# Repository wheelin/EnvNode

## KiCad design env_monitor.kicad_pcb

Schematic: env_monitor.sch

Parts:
C1, C2, C6, C7, C9, C12, C27, C28, C29, C30, C31, C32, C33, C34, C35: 1u; C_0805_HandSoldering
C3, C5, C22, C24: 4.7u; C_0805_HandSoldering
C4, C11, C13, C14, C16, C17, C19, C20, C23, C25: 100n; C_0805_HandSoldering
C8, C10: 47p; C_0805_HandSoldering
C15, C26: 10n; C_0805_HandSoldering
C18, C21: 20p; C_0805_HandSoldering
D1: LED_RGB; LED_RGB_PLCC-6
D2: RX_R; LED_0805_HandSoldering
D3: TX_G; LED_0805_HandSoldering
D4: BAT54KFILM; D_SOD-523
J1: Conn_01x02; JST_PH_B2B-PH-SM4-TB_02x2.00mm_Straight
J2: USB_B_Micro; USB_Micro-B_Molex_47346-0001
J3, J4: Conn_01x06; Pin_Header_Straight_1x06_Pitch2.54mm
J5: Micro_SD_Card_Det_Hirose_DM3AT; Hirose_DM3AT-SF-PEJM5
J6: Conn_01x03; MS12ANW03
L1: BKP2125HS600-T; L_0805_HandSoldering
R1, R2, R3, R8, R9, R12, R13, R14, R15, R16, R17, R20: 10k; R_0805_HandSoldering
R4: 20k; R_0805_HandSoldering
R5, R23: 750; R_0805_HandSoldering
R6, R7, R24: 330; R_0805_HandSoldering
R10, R22, R25, R28, R29, R32, R33: 47k; R_0805_HandSoldering
R11, R26, R27: 100k; R_0805_HandSoldering
R18: 4.7k; R_0805_HandSoldering
R19, R21: 27; R_0805_HandSoldering
SW1, SW2, SW4, SW5, SW6: SW_Push; SW_SPST_B3S-1000
U1: lmv341; SOT-23-6_Handsoldering
U2: TPS73633DBV; SOT-23-5_HandSoldering
U3: FT230XS; SSOP-16_3.9x4.9mm_Pitch0.635mm
U4: STM32L431CCTx; LQFP-48_7x7mm_Pitch0.5mm
U5: STLCS01V1; STLC01V1
U6: DOGM128X6; DOGM128E
Y1: Crystal_GND24; Crystal_SMD_Abracon_ABM3B-4pin_5.0x3.2mm

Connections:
FRX_MTX: U3.4, U4.21 (PB10)
FTX_MRX: U3.1, U4.22 (PB11)
IO_MCU_RST: C15.1, J3.5, R22.2, U4.7 (NRST)
IO_MCU_SWCLK: J3.2, U4.37 (PA14)
IO_MCU_SWDIO: J3.4, U4.34 (PA13)
LCD_CMD_DAT: U4.19 (PB1), U6.24
LCD_CS: R27.2, U4.18 (PB0), U6.26
LED_BLUE: R7.2, U4.31 (PA10)
LED_GREEN: R6.2, U4.30 (PA9)
LED_RED: R5.2, U4.29 (PA8)
unnamed: C3.1, D4.1, J1.1, J6.3, R3.1, U2.1 (IN)
unnamed: C8.1, J2.3, R19.2
unnamed: C10.1, J2.2, R21.2
unnamed: C11.1, U3.3, U3.10, U3.11
unnamed: C18.1, U4.5 (PH0), Y1.1
unnamed: C21.1, U4.6 (PH1), Y1.3
unnamed: C23.1, L1.1, U4.9 (VDDA)
unnamed: C27.1, C28.1, U6.16
unnamed: C27.2, U6.17
unnamed: C28.2, U6.15
unnamed: C29.1, U6.13
unnamed: C29.2, U6.14
unnamed: C30.1, U6.7
unnamed: C31.1, U6.8
unnamed: C32.1, U6.9
unnamed: C33.1, U6.10
unnamed: C34.1, U6.11
unnamed: C35.1, U6.18
unnamed: D1.4, R7.1
unnamed: D1.5, R6.1
unnamed: D1.6, R5.1
unnamed: D2.1, U3.14
unnamed: D2.2, R23.1
unnamed: D3.1, U3.7
unnamed: D3.2, R24.1
unnamed: J5.1 (DAT2), R33.2
unnamed: J5.8 (DAT1), R32.2
unnamed: J5.10 (DET_A), R28.2
unnamed: J6.2, R10.1, U2.3 (EN)
unnamed: R1.1, R8.2, SW1.2
unnamed: R2.1, R9.2, SW2.2
unnamed: R3.2, R4.1, U1.1
unnamed: R12.1, R14.2, SW4.2
unnamed: R13.1, R15.2, SW5.2
unnamed: R16.1, R17.2, SW6.2
unnamed: R19.1, U3.9
unnamed: R21.1, U3.8
unnamed: R26.2, U6.25
PB_CENTER: C9.1, R17.1, U4.45 (PB8)
PB_DOWN: C6.1, R14.1, U4.44 (PH3)
PB_LEFT: C2.1, R9.1, U4.43 (PB7)
PB_RIGHT: C7.1, R15.1, U4.42 (PB6)
PB_UP: C1.1, R8.1, U4.46 (PB9)
SD_CARD_CS: J5.2 (DAT3/CD), R29.2, U4.13 (PA3)
SD_CARD_DET: J5.9 (DET_B), U4.14 (PA4)
SENSOR_MCU_CS: U4.33 (PA12), U5.11
SENSOR_MCU_INT: U4.32 (PA11), U5.12
SENSOR_MCU_RST: C26.1, J4.5, R25.2, U5.14
SENSOR_MCU_SWCLK: J4.2, U5.15
SENSOR_MCU_SWDIO: J4.4, U5.16
SPI1_MISO: J5.7 (DAT0), U4.16 (PA6)
SPI1_MOSI: J5.3 (CMD), U4.17 (PA7), U6.22
SPI1_SCK: J5.5 (CLK), U4.15 (PA5), U6.23
SPI3_MISO: U4.40 (PB4), U5.9
SPI3_MOSI: U4.41 (PB5), U5.10
SPI3_SCK: U4.39 (PB3), U5.8
USB_VBUS_DET: R18.1, R20.2, U3.16
VBATT_ENABLE: R11.1, U1.5, U4.12 (PA2)
VBATT_MEASURE: U1.3, U1.4, U4.11 (PA1)
VCC: C4.1, C5.1, C12.1, C13.1, C14.1, C16.1, C17.1, C19.1, C20.1, C22.1, C24.1, C25.1, J3.1, J4.1, J5.4 (VDD), L1.2, R22.1, R23.2, R24.2, R25.1, R26.1, R27.1, R28.1, R29.1, R32.1, R33.1, SW1.1, SW2.1, SW4.1, SW5.1, SW6.1, U1.6, U2.5 (OUT), U3.12, U4.1 (VBAT), U4.24 (VDD), U4.36 (VDDUSB), U4.48 (VDD), U5.3, U5.4, U6.20, U6.21
VUSB: D4.2, J2.1, R18.2

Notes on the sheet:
TIM1_CH1
TIM1_CH2
TiM1_CH3
ADC1_IN6
AAAF3529LSEEZGKQBKS
PTS645SM43SMTR92
FY0800018
APT2012LSECK/J3-PRV
APT2012LZGCK
B2B-PH-SM4-TBT(LF)(SN)

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
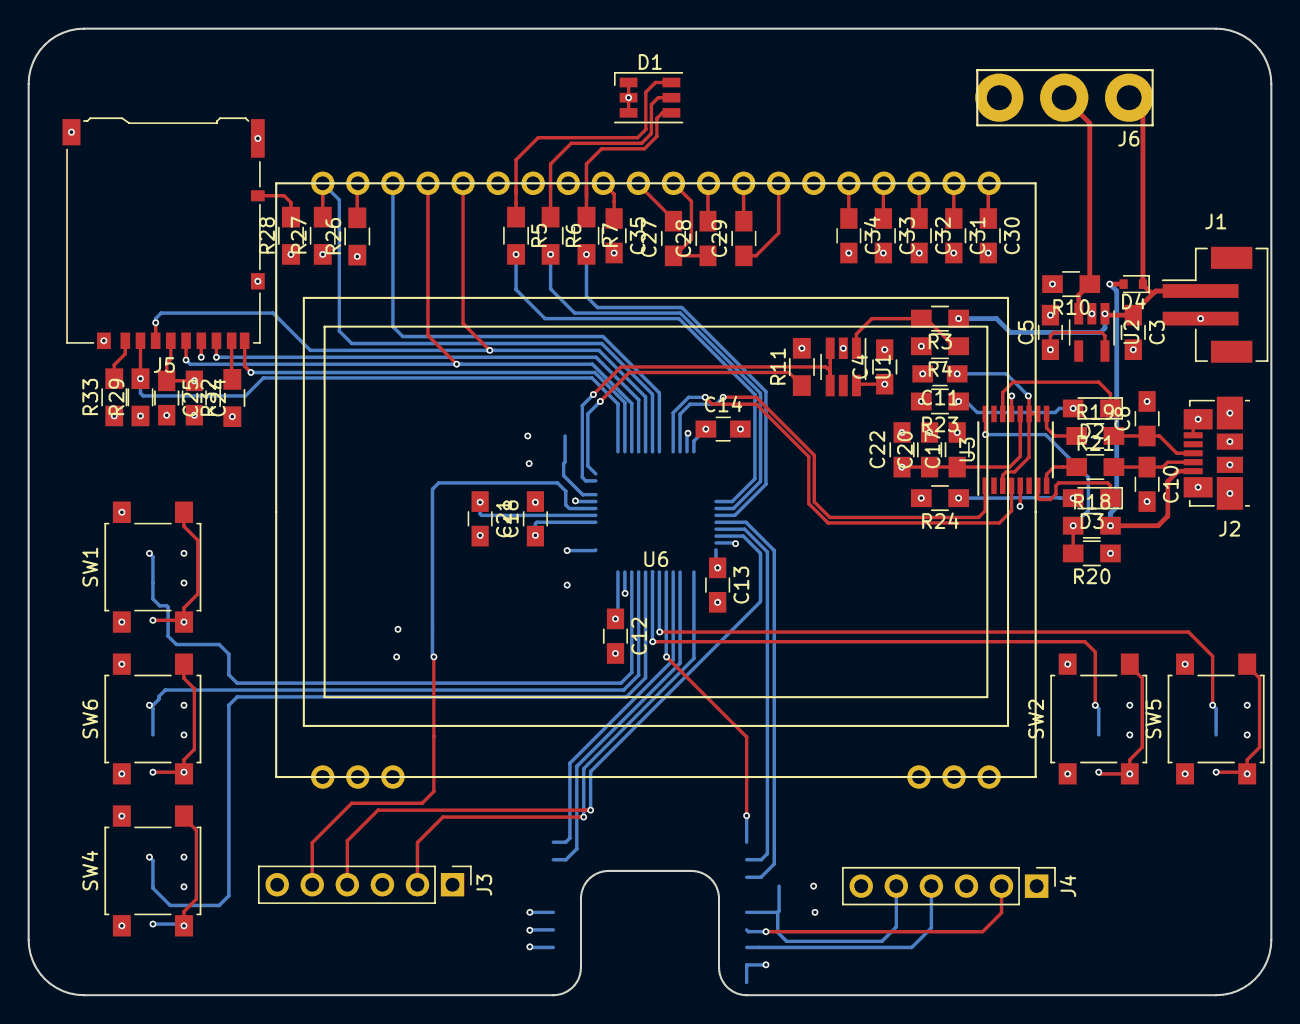
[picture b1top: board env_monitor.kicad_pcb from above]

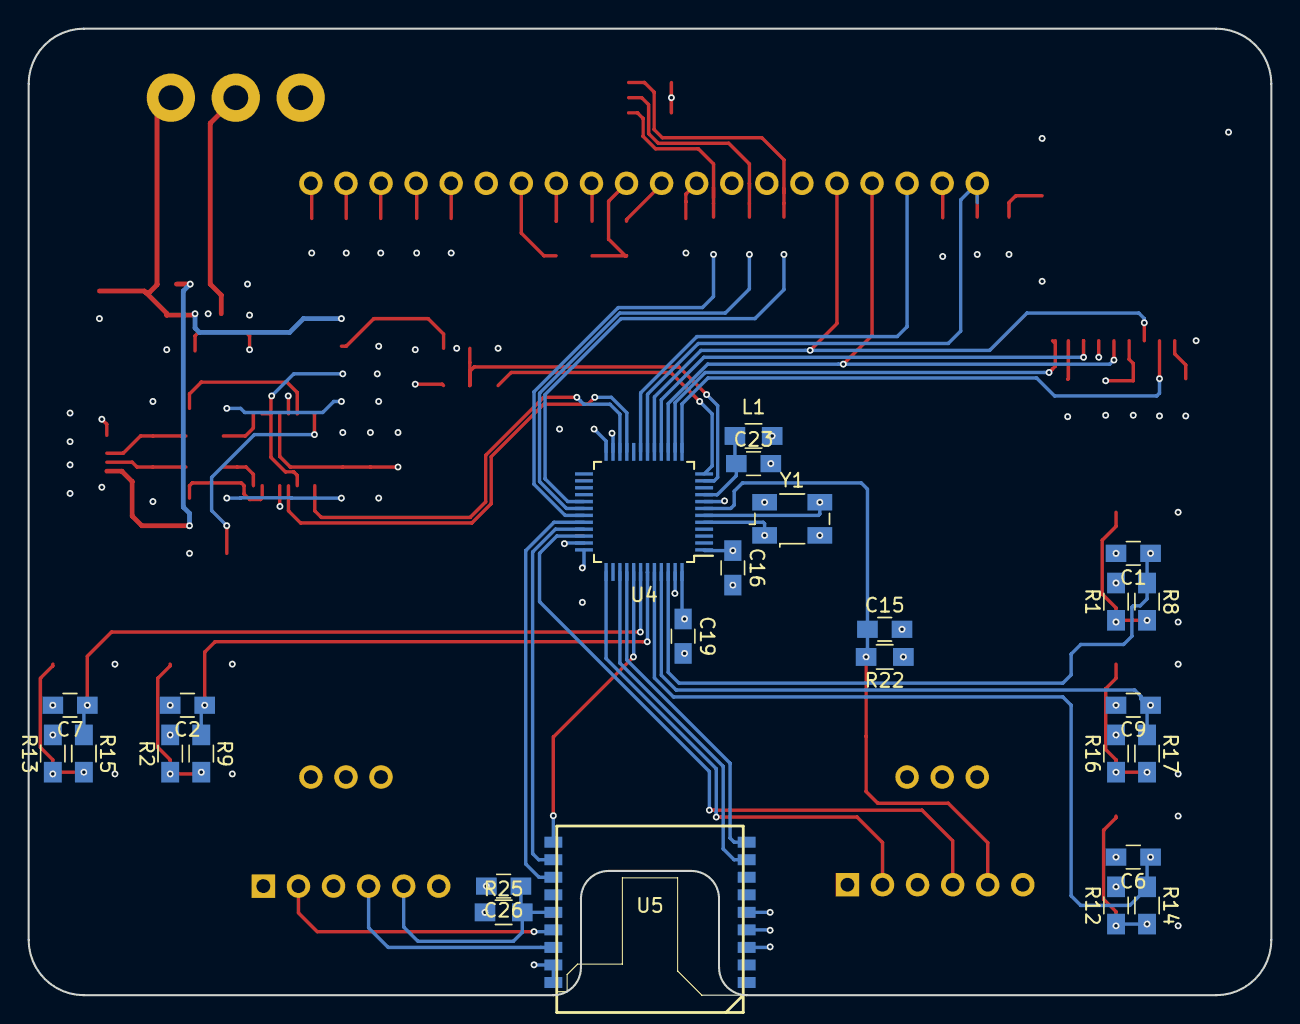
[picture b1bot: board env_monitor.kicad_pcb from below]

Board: 4 copper layers, 90.0 x 70.0 mm, 89 parts (26 on the bottom side), 72 nets.

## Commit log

2018-08-23 upload envmonitor files
